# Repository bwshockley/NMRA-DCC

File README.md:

# NMRA-DCC
NMRA DCC based Controllers and Decoders PCB designs.

##Components

Please see the README.md file for each component inside the repository.  The files included are board and schematic files for [CADSoft Eagle](http://www.cadsoftusa.com/)

##Usage

Feel free to use, update, and change the files as you want.  Please keep in mind these files were created with a hobby license and as such should never be used for commercial purposes.

##Installation

Download and install Eagle first, then download each component files.  Open and modify as needed.

##Build

If you want a physical board, you may use any one of a number of suppliers.  I typically use [OSHPark.](https://oshpark.com/)

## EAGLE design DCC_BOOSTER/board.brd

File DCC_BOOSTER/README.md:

#DCC Booster Shield for Arduino#

This is an Arduino Uno R3 compatible sheild that generates a boosted track level signal for Digital Command Control of model
railroads.  This shield is based off the [Railstars RAILbooster](https://github.com/Railstars/RAILbooster) and the LMD18200
H-bridge.  Included in this design is feedback on DCC signal, overtemp, and over current as well as shut-down protection for
each of those feedback components.  This booster can support 3A to the rails.

In order to use it, please see the [CmdrArduino](https://github.com/Railstars/CmdrArduino) code.  You will need to load the
Arduino source code onto a Arduino UNO R3 or compatible board.  Signal for the DCC control is sent via digital Pin #10.

The Uno can also act as ISP for the ATTINY44 on this board for feedback and shut-down protection.

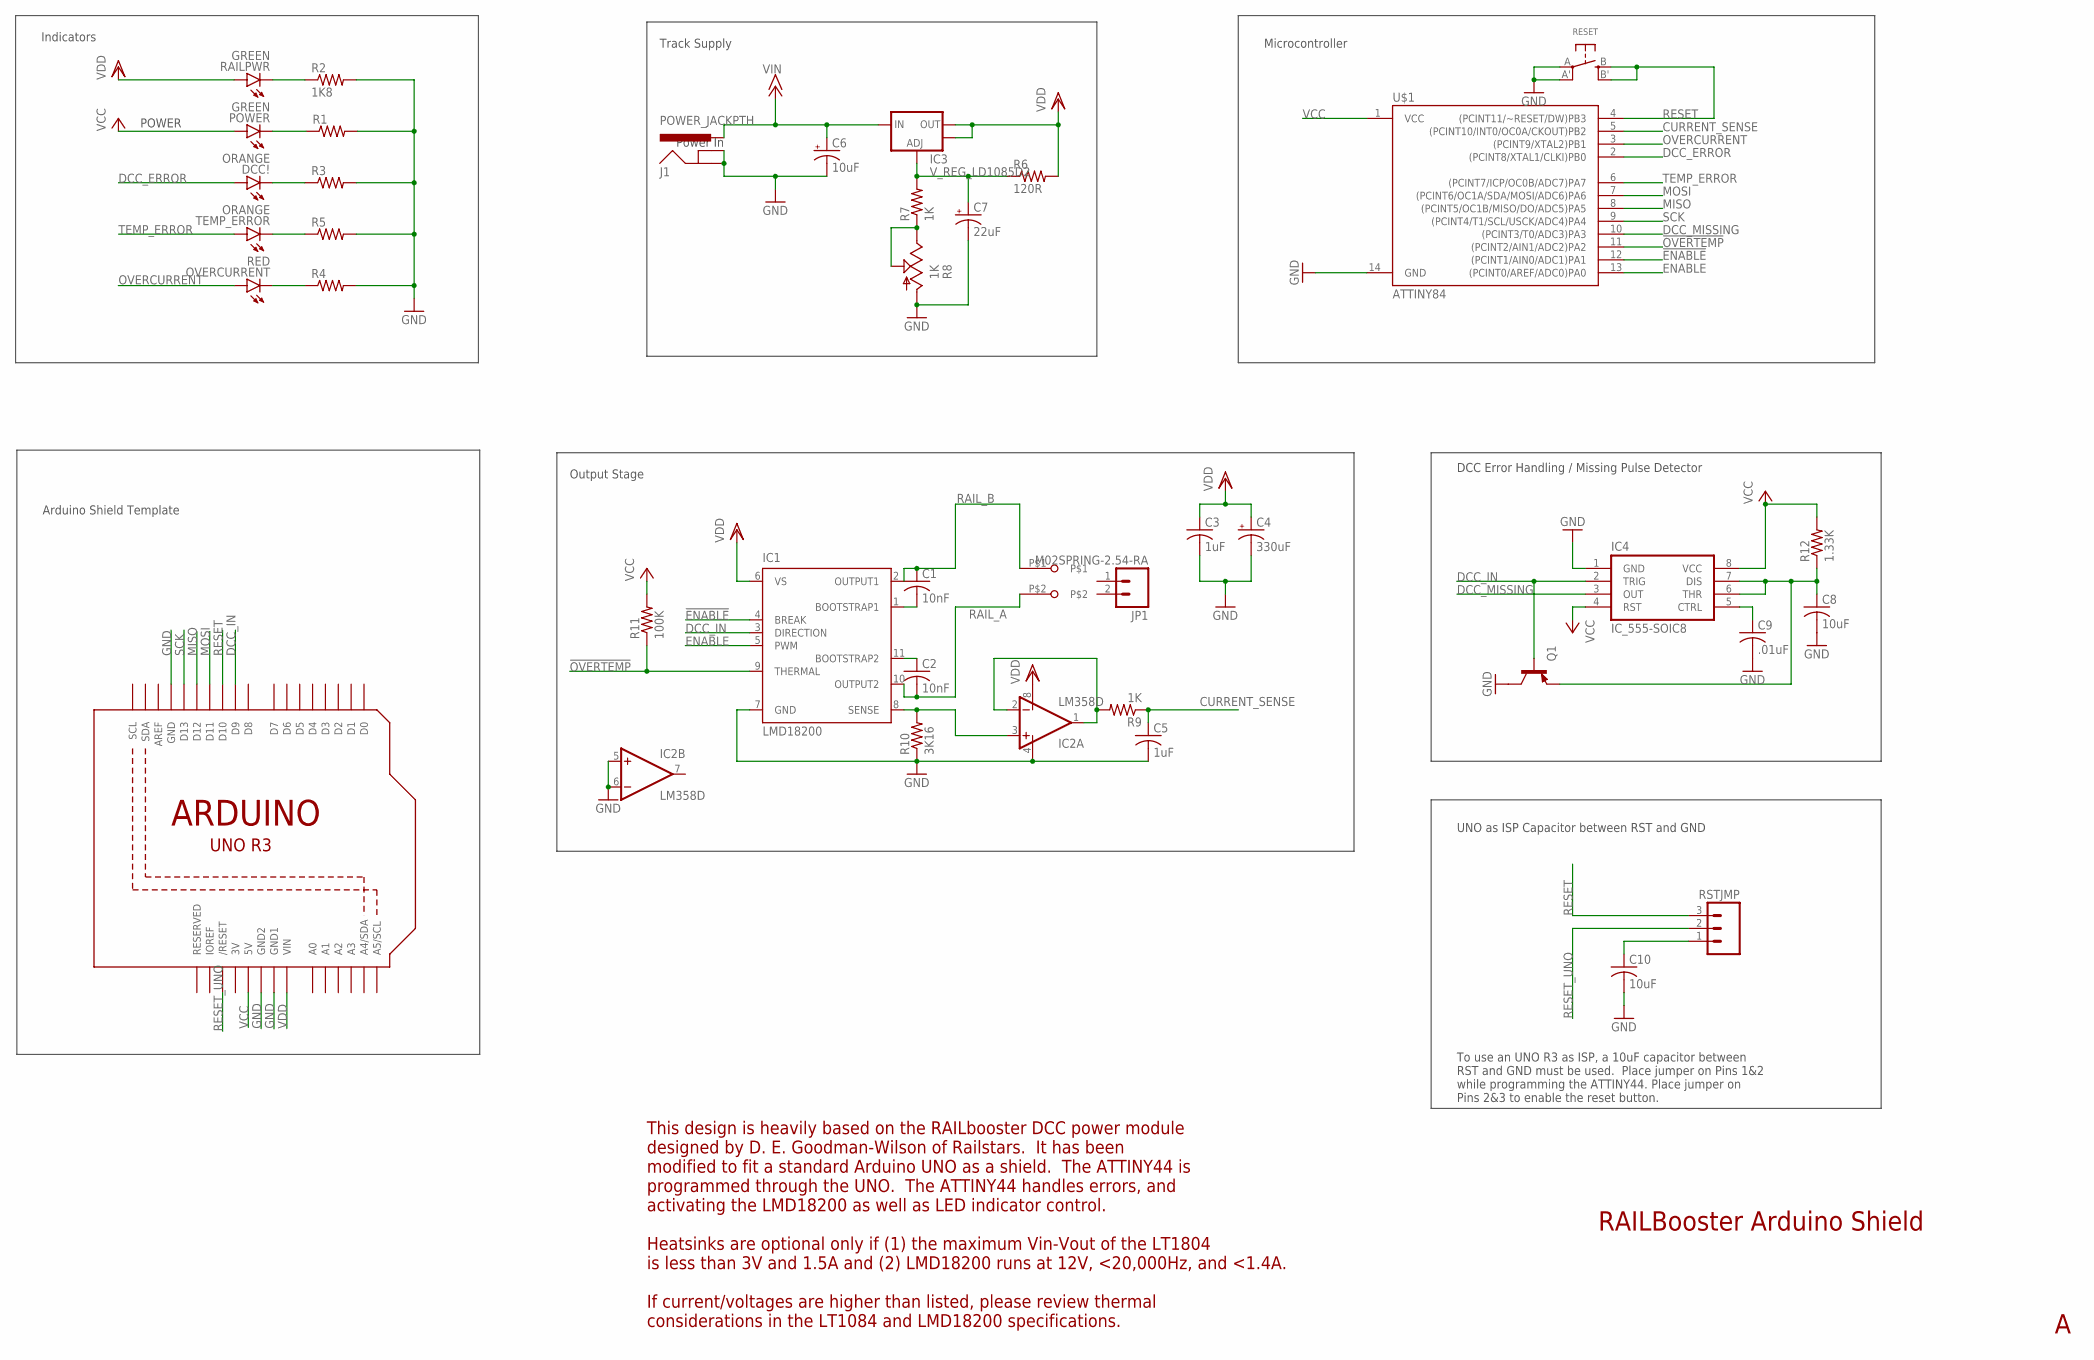
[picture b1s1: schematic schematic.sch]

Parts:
C1, C2: 10nF; C1206
C3, C5: 1uF; C1206
C4: 330uF; E5-10,5
C6: 10uF; E2-5
C7: 22uF; E2-5
C8, C10: 10uF; C1206
C9: .01uF; C1206
DCC!: ORANGE; LED-1206
IC1: LMD18200; TO-220-11
IC2: LM358D; SO08
IC3: V_REG_LD1085D2; D2PACK/A
IC4: IC_555-SOIC8; SOIC-8
J1: POWER_JACKPTH; POWER_JACK_PTH
JP1: M02SPRING-2.54-RA; SPRINGTERMINAL-2.54MM-2
OVERCURRENT: RED; LED-1206
POWER: GREEN; LED-1206
Q1: TRANSISTOR_BJT_PNP-SOT-23-BCE; SOT-23
R1, R3, R4, R5: RESISTOR1206; 1206
R2: 1K8; 1206
R6: 120R; 1206
R7, R9: 1K; 1206
R8: 1K; S64W
R10: 3K16; 1206
R11: 100K; 1206
R12: 1.33K; 1206
RAILPWR: GREEN; LED-1206
RESET: SWITCH_TACT_SMT; EVQ-Q2
RSTJMP: M03PTH; 1X03
TEMP_ERROR: ORANGE; LED-1206
U1: ARDUINOR3-DIMENSION; ARDUINOR3
U$1: ATTINY84; SO14
X4: SCREWTERMINAL-5.08-2

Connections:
3V: U1.3V
!ENABLE: IC1.4 (BREAK), U$1.12 ((PCINT1/AIN0/ADC1)PA1)
!OVERTEMP: IC1.9 (THERMAL), R11.1, U$1.11 ((PCINT2/AIN1/ADC2)PA2)
CTRL: C9.1, IC4.5 (CTRL)
CURRENT_SENSE: C5.1, R9.1, U$1.5 ((PCINT10/INT0/OC0A/CKOUT)PB2)
CURRENT_SENSE_UNBUFFERED: IC2.1 (OUT), IC2.2 (-IN), R9.2
DCC_ERROR: DCC!.A, U$1.2 ((PCINT8/XTAL1/CLKI)PB0)
DCC_IN: IC1.3 (DIRECTION), IC4.2 (TRIG), Q1.1 (B), U1.D9
DCC_MISSING: IC4.3 (OUT), U$1.10 ((PCINT3/T0/ADC3)PA3)
ENABLE: IC1.5 (PWM), U$1.13 ((PCINT0/AREF/ADC0)PA0)
GND: C3.2, C4.-, C5.2, C6.-, C7.-, C8.2, C9.2, C10.2, IC1.7 (GND), IC2.4 (V-), IC2.5 (+IN), IC2.6 (-IN), IC4.1 (GND), J1.GND, J1.GNDBREAK, Q1.2 (C), R1.2, R2.2, R3.2, R4.2, R5.2, R8.A, R10.1, RESET.A, RESET.A' (P1), U1.GND, U1.GND1, U1.GND2, U$1.14 (GND)
MISO: U1.D12, U$1.8 ((PCINT5/OC1B/MISO/DO/ADC5)PA5)
MOSI: U1.D11, U$1.7 ((PCINT6/OC1A/SDA/MOSI/ADC6)PA6)
unnamed: R7.1, R8.E, R8.S
unnamed: C1.2, IC1.1 (BOOTSTRAP1)
unnamed: C2.1, IC1.11 (BOOTSTRAP2)
unnamed: IC1.8 (SENSE), IC2.3 (+IN), R10.2
unnamed: POWER.C, R1.1
unnamed: C7.+, IC3.1 (ADJ), R6.1, R7.2
unnamed: C10.1, RSTJMP.1
unnamed: DCC!.C, R3.1
unnamed: R5.1, TEMP_ERROR.C
unnamed: R2.1, RAILPWR.C
unnamed: C8.1, IC4.6 (THR), IC4.7 (DIS), Q1.3 (E), R12.1
unnamed: OVERCURRENT.C, R4.1
OVERCURRENT: OVERCURRENT.A, U$1.3 ((PCINT9/XTAL2)PB1)
RAIL_A: C2.2, IC1.10 (OUTPUT2), X4.P$2
RAIL_B: C1.1, IC1.2 (OUTPUT1), X4.P$1
RESET: RESET.B (S), RESET.B' (S1), RSTJMP.3, U1.D10, U$1.4 ((PCINT11/~RESET/DW)PB3)
RESET_UNO: RSTJMP.2, U1.RESET (/RESET)
SCK: U1.D13, U$1.9 ((PCINT4/T1/SCL/USCK/ADC4)PA4)
TEMP_ERROR: TEMP_ERROR.A, U$1.6 ((PCINT7/ICP/OC0B/ADC7)PA7)
VCC: IC4.4 (RST), IC4.8 (VCC), POWER.A, R11.2, R12.2, U1.5V, U$1.1 (VCC)
VDD: C3.1, C4.+, IC1.6 (VS), IC2.8 (V+), IC3.2 (OUT), IC3.TAB (OUT), R6.2, RAILPWR.A, U1.VIN
VIN: C6.+, IC3.3 (IN), J1.PWR

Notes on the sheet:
Track Supply
Power In
Indicators
Output Stage
POWER
Arduino Shield Template
RAILBooster Arduino Shield
This design is heavily based on the RAILbooster DCC power module designed by D. E. Goodman-Wilson of Railstars. It has been modified to fit a standard Arduino UNO as a shield. The ATTINY44 is programmed through the UNO. The ATTINY44 handles errors, and activating the LMD18200 as well as LED indicat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
Microcontroller
DCC Error Handling / Missing Pulse Detector
UNO as ISP Capacitor between RST and GND
To use an UNO R3 as ISP, a 10uF capacitor between RST and GND must be used. Place jumper on Pins 1&2 while programming the ATTINY44. Place jumper on Pins 2&3 to enable the reset button.

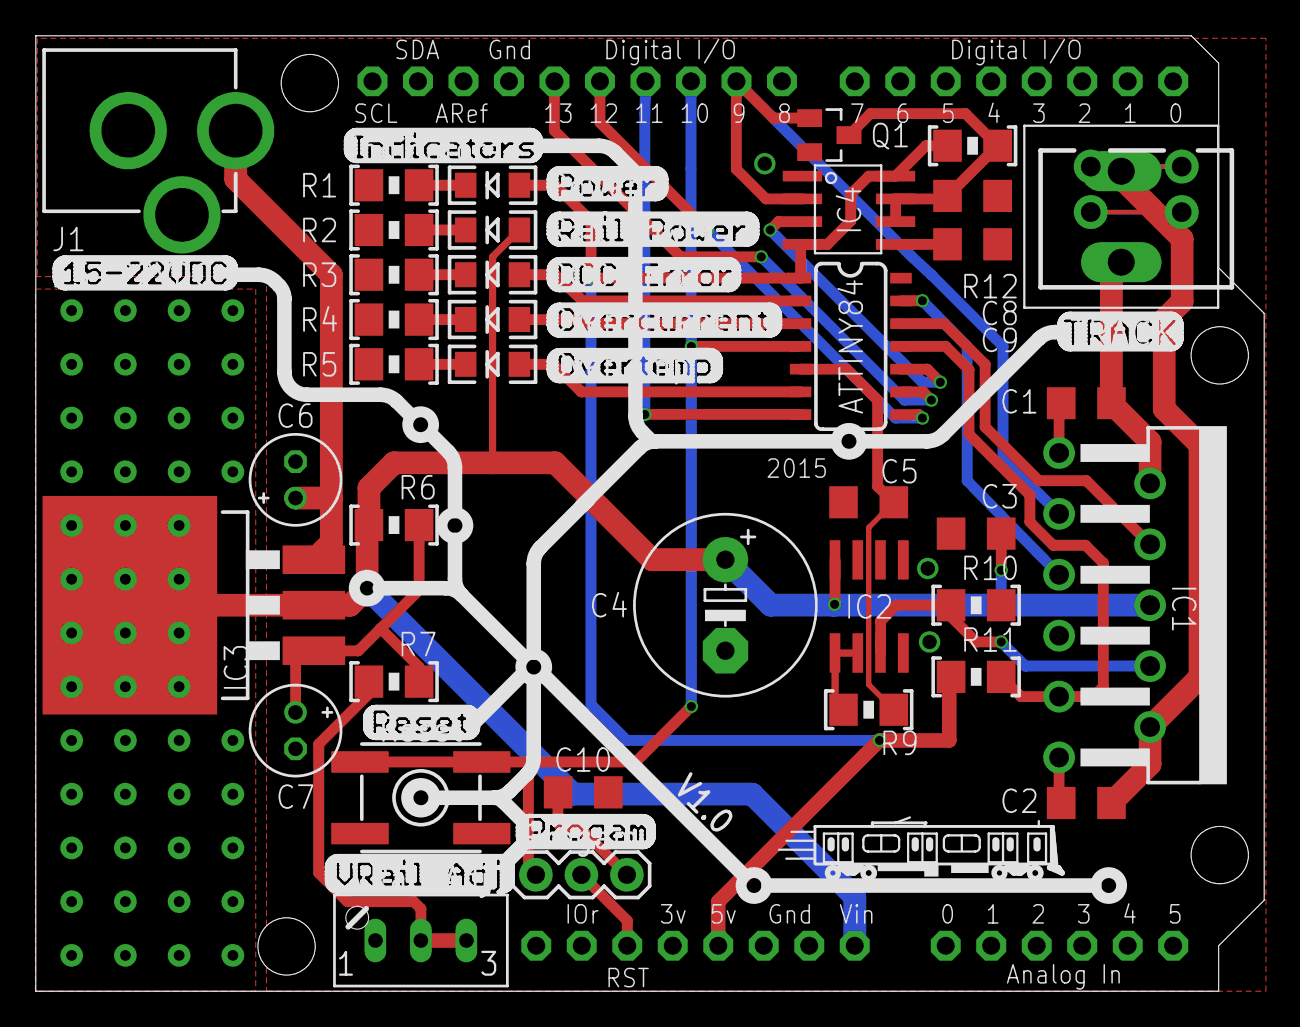
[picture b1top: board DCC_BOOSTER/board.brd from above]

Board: 2 copper layers, 68.6 x 53.3 mm, 39 parts (0 on the bottom side), 34 nets.

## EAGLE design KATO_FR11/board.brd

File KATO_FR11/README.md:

This is a DIY replacment for the KATO FR11 DCC controlled interior light decoder.  It is designed as a direct drop-in replacement
for the FR11 part.  It is based off the ATTINY85 microcontroller.

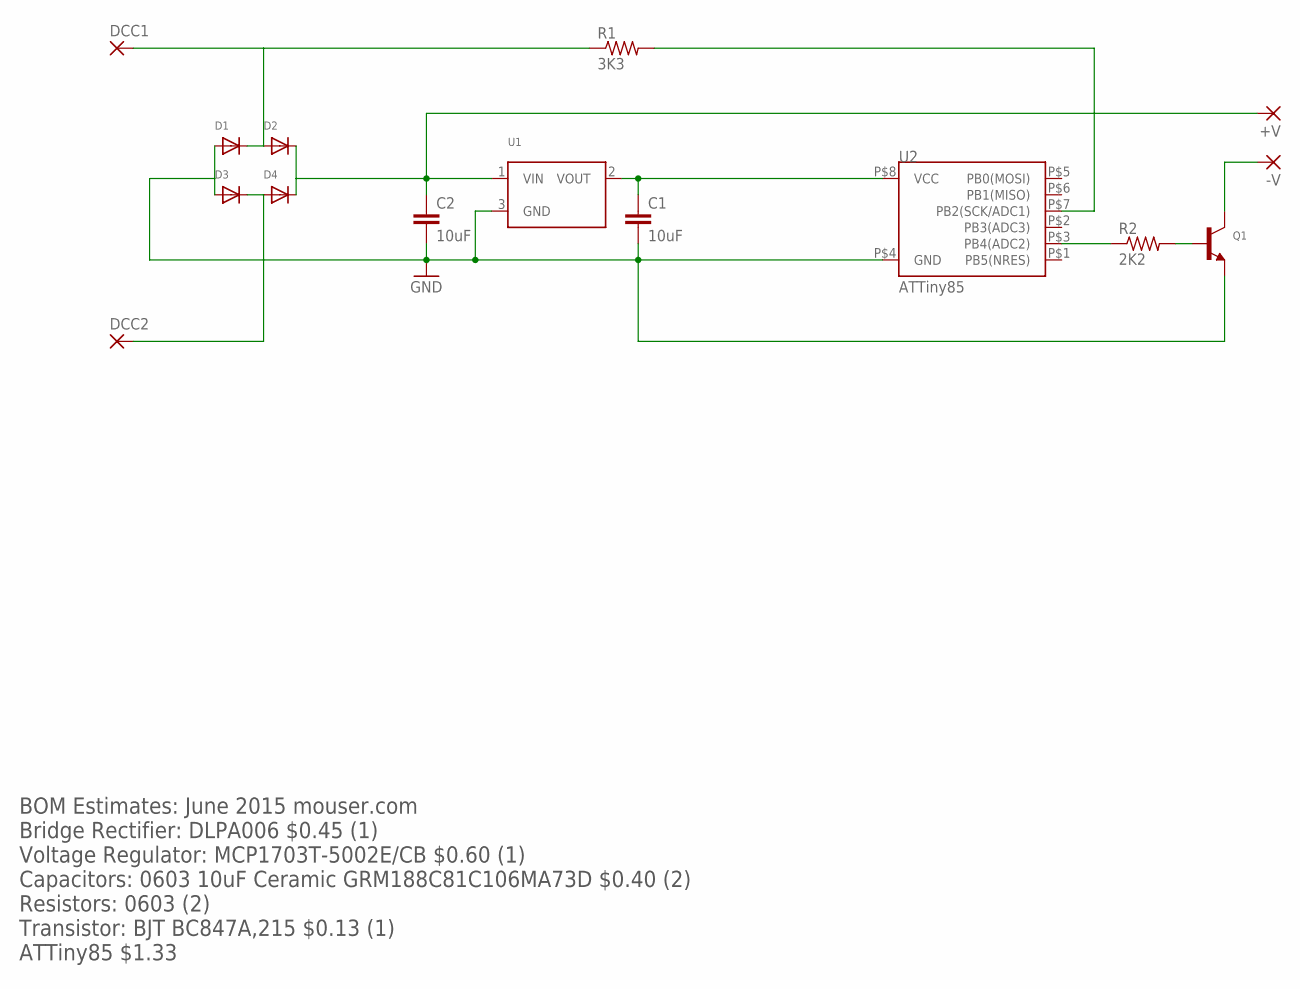
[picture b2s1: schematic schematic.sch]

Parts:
+V: FR11_PAD6MMX2MM; SMD6MMX2MM
-V: FR11_PAD6MMX2MM; SMD6MMX2MM
C1, C2: 10uF; C0402
D1, D2, D3, D4: DIODESOD-523; SOD-523
DCC1, DCC2: FR11_PAD6MMX2MM; SMD6MMX2MM
Q1: TRANSISTOR_NPN; SOT23-R
R1: 3K3; R0402
R2: 2K2; R0402
U1: VREG_SOT23; SOT23-R
U2: ATTiny85; SOIC-8_SMALL

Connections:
GND: C1.2, C2.2, D1.A, D3.A, Q1.2 (E), U1.3 (GND), U2.P$4 (GND)
unnamed: R2.1, U2.P$3 (PB4(ADC2))
unnamed: R1.2, U2.P$7 (PB2(SCK/ADC1))
unnamed: -V.P$1, Q1.3 (C)
unnamed: Q1.1 (B), R2.2
unnamed: C1.1, U1.2 (VOUT), U2.P$8 (VCC)
VIN: +V.P$1, C2.1, D2.K (C), D4.K (C), U1.1 (VIN)
XT1: D1.K (C), D2.A, DCC1.P$1, R1.1
XT2: D3.K (C), D4.A, DCC2.P$1

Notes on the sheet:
BOM Estimates: June 2015 mouser.com Bridge Rectifier: DLPA006 $0.45 (1) Voltage Regulator: MCP1703T-5002E/CB $0.60 (1) Capacitors: 0603 10uF Ceramic GRM188C81C106MA73D $0.40 (2) Resistors: 0603 (2) Transistor: BJT BC847A,215 $0.13 (1) ATTiny85 $1.33

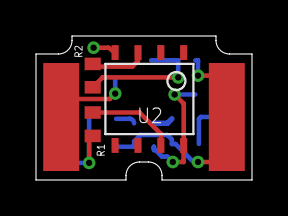
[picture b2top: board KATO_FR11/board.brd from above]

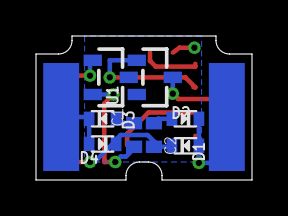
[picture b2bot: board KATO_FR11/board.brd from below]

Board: 2 copper layers, 12.0 x 8.0 mm, 15 parts (10 on the bottom side), 9 nets.

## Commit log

2015-07-17 Initial Commit
    This is the initial commit of the hardware board file.
2015-07-17 Initial Commit
    This is the initial commit of the hardware schematic.
2015-07-17 Update with Routing
2015-11-24 Update README.md
    Updated with additional general information about repository, tools used to create the files, and source for obtaining PCBs.

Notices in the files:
parts and their libraries:
SparkFun-PowerIC: Licensing: Creative Commons ShareAlike 4.0 International - https://creativecommons.org/licenses/by-sa/4.0
microbuilder: This work is placed in the public domain, and may be freely used for commercial and non-commercial work with the following conditions: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
